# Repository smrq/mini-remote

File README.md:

# mini-remote

Tiny universal remote PCB and firmware

## PCB

The design for the PCB was done in KiCad. The PCB is designed according to the specifications of manufacturing with [JLCPCB](https://jlcpcb.com/).

### BOM

Microcontroller

* **U1** [STMicroelectronics STM8L101F3P3](https://www.mouser.com/ProductDetail/511-STM8L101F3P3)
	* STM8L101F3P6 is fine too
	* Any STM8L101FxPy is probably ok as long as the firmware can be squished to fit

LEDs

* **D1** [940nm IR LED (Everlight IR333/H0/L10)](https://www.mouser.com/ProductDetail/638-IR333-H0-L10)
* **D2** [2x3x4 LED, red (Chanzon)](https://www.amazon.com/Rectangle-Diffused-Lighting-Electronics-Components/dp/B01C3ZZT1E)
	* Or whatever LEDs you have lying around really

Resistors

* **R1** 22Ω 0805 resistor
* **R2** 2K7Ω 0805 resistor
* **R3** 1KΩ 0805 resistor
* **R4** 10KΩ 0805 resistor

Capacitors

* **C1-C2** 100nF 0805 capacitor

Transistors

* **Q1** [MMBT3906 PNP transistor](https://www.mouser.com/ProductDetail/863-MMBT3906LT3G)

Etc.

* **SW1-SW22** 20x [E-Switch LL3301NF065QG](https://www.mouser.com/ProductDetail/612-LL3301NF065QG)
	* Note that SW2 and SW9 are omitted from this design
* **BT1** [Linx Technologies BAT-HLD-001 CR2032 battery holder](https://www.mouser.com/ProductDetail/712-BAT-HLD-001)
* **J1** 4-pin 2.54mm header (for programming the microcontroller)
* **J2** 2-pin 2.54mm header (optional, for debugging only)

## Firmware

Building the firmware is done with Docker, but flashing the firmware requires USB hardware access that is beyond my Docker capabilities, if it is possible at all.

Prerequisites:

* Install Docker
* Install [stm8flash](https://github.com/vdudouyt/stm8flash) and make sure it is in your PATH
* Run `make docker` to build the Docker image

Building and flashing:

* `make` to build the firmware hex file
* `make flash` to flash the firmware

I used [this cheap knockoff ST-Link V2 programmer (HiLetgo V2)](https://www.amazon.com/HiLetgo-Emulator-Downloader-Programmer-STM32F103C8T6/dp/B07SQV6VLZ/ref=sr_1_5?dchild=1&keywords=st-link+v2&qid=1620240018&sr=8-5) with no problems.

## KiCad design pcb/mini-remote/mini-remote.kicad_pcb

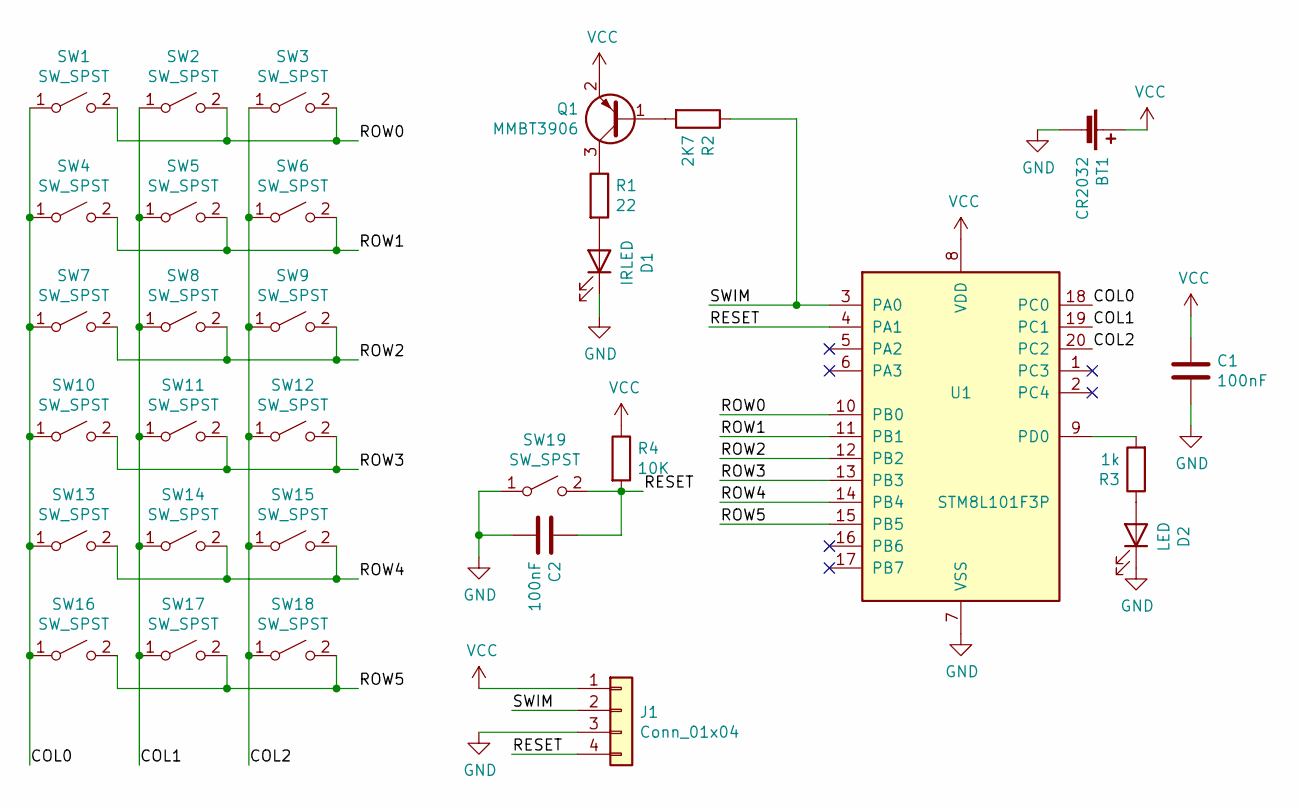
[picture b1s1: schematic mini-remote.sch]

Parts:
BT1: CR2032; BATHLD001
C1, C2: 100nF; C_0805_2012Metric
D1: IRLED; LED_D5.0mm
D2: LED; LED_Rectangular_W3.0mm_H2.0mm
J1: Conn_01x04; PinHeader_1x04_P2.54mm_Vertical
Q1: MMBT3906; SOT-23
R1: 22; R_0805_2012Metric
R2: 2K7; R_0805_2012Metric
R3: 1k; R_Axial_DIN0207_L6.3mm_D2.5mm_P7.62mm_Horizontal
R4: 10K; R_0805_2012Metric
SW1, SW2, SW3, SW4, SW5, SW6, SW7, SW8, SW9, SW10, SW11, SW12, SW13, SW14, SW15, SW16, SW17, SW18, SW19: SW_SPST; LL3301NF065QG
U1: STM8L101F3P; TSSOP-20_4.4x6.5mm_P0.65mm

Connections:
/COL0: SW1.1 (A), SW4.1 (A), SW7.1 (A), SW10.1 (A), SW13.1 (A), SW16.1 (A), U1.18 (PC0)
/COL1: SW2.1 (A), SW5.1 (A), SW8.1 (A), SW11.1 (A), SW14.1 (A), SW17.1 (A), U1.19 (PC1)
/COL2: SW3.1 (A), SW6.1 (A), SW9.1 (A), SW12.1 (A), SW15.1 (A), SW18.1 (A), U1.20 (PC2)
/RESET: C2.1, J1.4, R4.2, SW19.2 (B), U1.4 (PA1)
/ROW0: SW1.2 (B), SW2.2 (B), SW3.2 (B), U1.10 (PB0)
/ROW1: SW4.2 (B), SW5.2 (B), SW6.2 (B), U1.11 (PB1)
/ROW2: SW7.2 (B), SW8.2 (B), SW9.2 (B), U1.12 (PB2)
/ROW3: SW10.2 (B), SW11.2 (B), SW12.2 (B), U1.13 (PB3)
/ROW4: SW13.2 (B), SW14.2 (B), SW15.2 (B), U1.14 (PB4)
/ROW5: SW16.2 (B), SW17.2 (B), SW18.2 (B), U1.15 (PB5)
/SWIM: J1.2, R2.1, U1.3 (PA0)
GND: BT1.2 (-), C1.2, C2.2, D1.1 (K), D2.1 (K), J1.3, SW19.1 (A), U1.7 (VSS)
unnamed: D1.2 (A), R1.2
unnamed: D2.2 (A), R3.1
unnamed: Q1.1 (B), R2.2
unnamed: Q1.3 (C), R1.1
unnamed: R3.2, U1.9 (PD0)
VCC: BT1.1 (+), C1.1, J1.1, Q1.2 (E), R4.1, U1.8 (VDD)

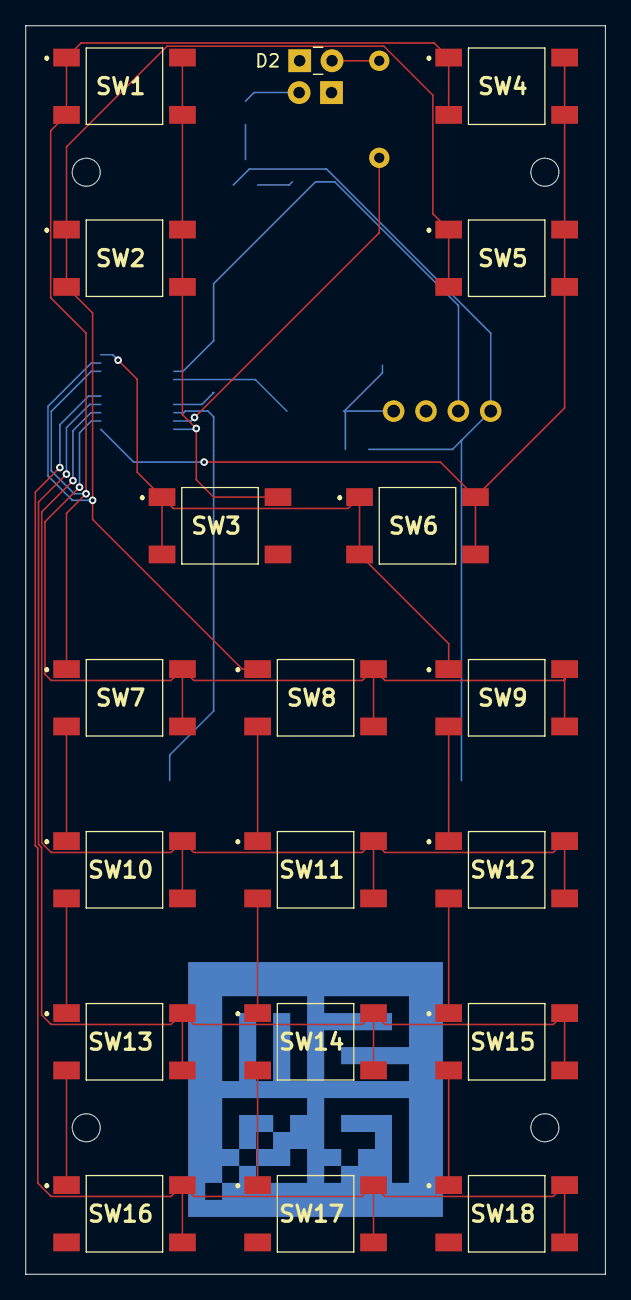
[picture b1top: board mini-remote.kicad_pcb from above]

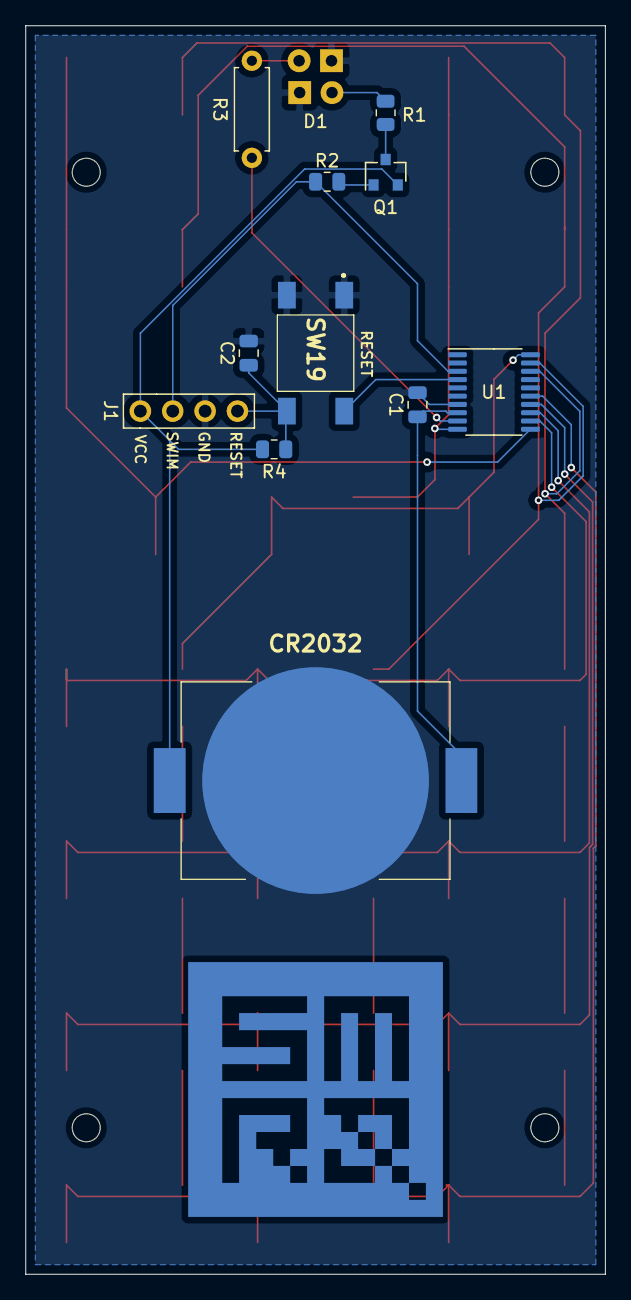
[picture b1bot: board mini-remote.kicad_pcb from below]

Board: 2 copper layers, 45.5 x 98.0 mm, 31 parts (12 on the bottom side), 18 nets.

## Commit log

2021-05-06 Initial PCB design
2021-05-06 Blink firmware
2021-05-08 Fix pcb error
2021-05-08 Some pin assignments
2021-05-08 Blink from button input
2021-05-10 Working single button remote
2021-05-10 PCB version 1
2021-05-12 Makefile cleaning
2021-05-12 README.md
2021-05-12 Fix wrong footprint in schematic
2021-05-25 Program all the buttons
2021-05-25 Fix issue with Samsung
2021-05-25 Update button layout
2021-05-31 Move pcb files
2021-06-01 Case model
2021-06-10 Adjust case model tolerances
2021-06-10 Case model v1.1
2021-06-10 Case model v1.2
2021-06-11 Case model v1.3
2021-07-21 Case model v1.4
2021-07-21 Case model v1.5
